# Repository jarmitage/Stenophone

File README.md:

# The Stenophone

As you can see this hasn't been worked on in a while. Nevertheless I still think about it and perhaps someone found it interesting to read so it's still here.

---

A musical instrument combining [live coding](http://toplap.org) and [stenotype](https://en.wikipedia.org/wiki/Stenotype).

Developed in the [Augmented Instruments Laboratory](http://instrumentslab.org) by [Jack Armitage](http://jackarmitage.com).

Presented at the [International Conference on Live Coding 2017](http://iclc.livecodenetwork.org/2017/), Morelia, Mexico. ([Article PDF](https://github.com/jarmitage/stenophone/raw/master/docs/stenophone_iclc2017.pdf))

## Abstract

Though laptop live coders are known to use other devices and instruments and play with other musicians, laptop live coding generally shares the common physical interface of the QWERTY keyboard. This project seeks to provide a means to explore alternatives to the QWERTY keyboard as a physical interface to laptop live coding. We present a live coding keyboard which is also a digital musical instrument, called the Stenophone. The Stenophone is an augmented stenotype or chorded keyboard, which permits continuous gestural control of keys and features an ergonomic design. These capabilities are exploited to enable the manipulation of algorithms and their parameterisation simultaneously.

## System diagram

Left: Top-down view of the Stenophone with top chassis removed, annotated with type letters and sensor/marker locations. Right: Diagram of system from mechanical input to live coding.

## Web app gif

## Citation

```bibtex
@inproceedings{armitage_stenophone:_2017,
	title = {The {Stenophone}: live coding on a chorded keyboard with continuous control},
	author = {Armitage, Jack and McPherson, Andrew},
	booktitle = {Proceedings of the {International} {Conference} on {Live} {Coding}},
	address = {Morelia, Mexico},
	url = {http://iclc.livecodenetwork.org/2017/},
	year = {2017},
	month = dec
}
```

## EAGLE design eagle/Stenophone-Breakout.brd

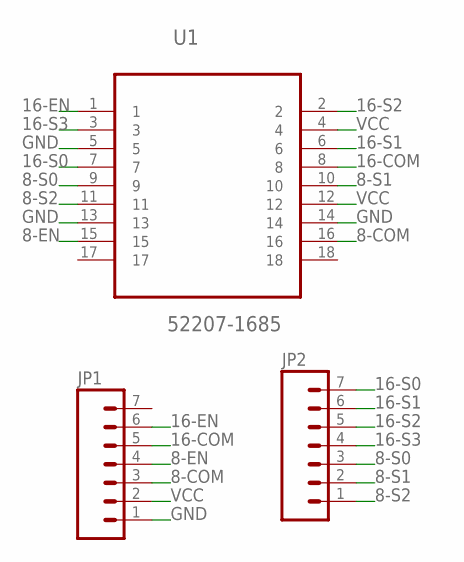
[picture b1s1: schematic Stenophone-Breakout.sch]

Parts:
JP1, JP2: M07; 1X07
U1: 52207-1685; MOLEX_52207-1685

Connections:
8-COM: JP1.3, U1.16
8-EN: JP1.4, U1.15
8-S0: JP2.3, U1.9
8-S1: JP2.2, U1.10
8-S2: JP2.1, U1.11
16-COM: JP1.5, U1.8
16-EN: JP1.6, U1.1
16-S0: JP2.7, U1.7
16-S1: JP2.6, U1.6
16-S2: JP2.5, U1.2
16-S3: JP2.4, U1.3
GND: JP1.1, U1.5, U1.13, U1.14
VCC: JP1.2, U1.4, U1.12

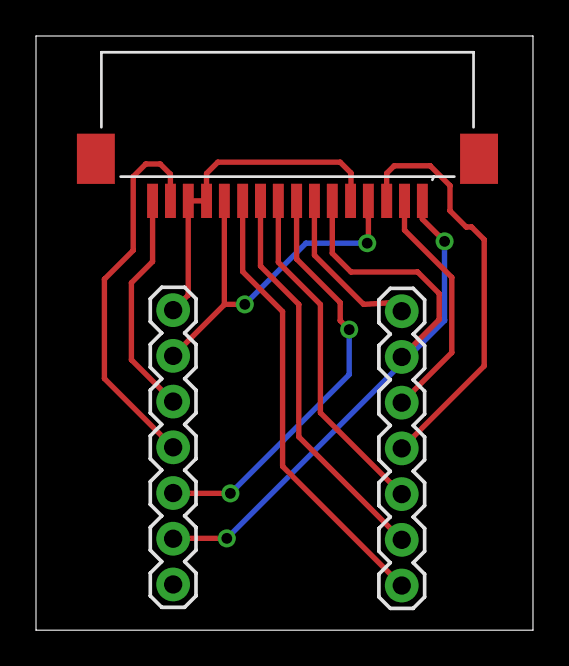
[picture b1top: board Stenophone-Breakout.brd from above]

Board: 2 copper layers, 27.6 x 33.0 mm, 3 parts (0 on the bottom side), 13 nets.

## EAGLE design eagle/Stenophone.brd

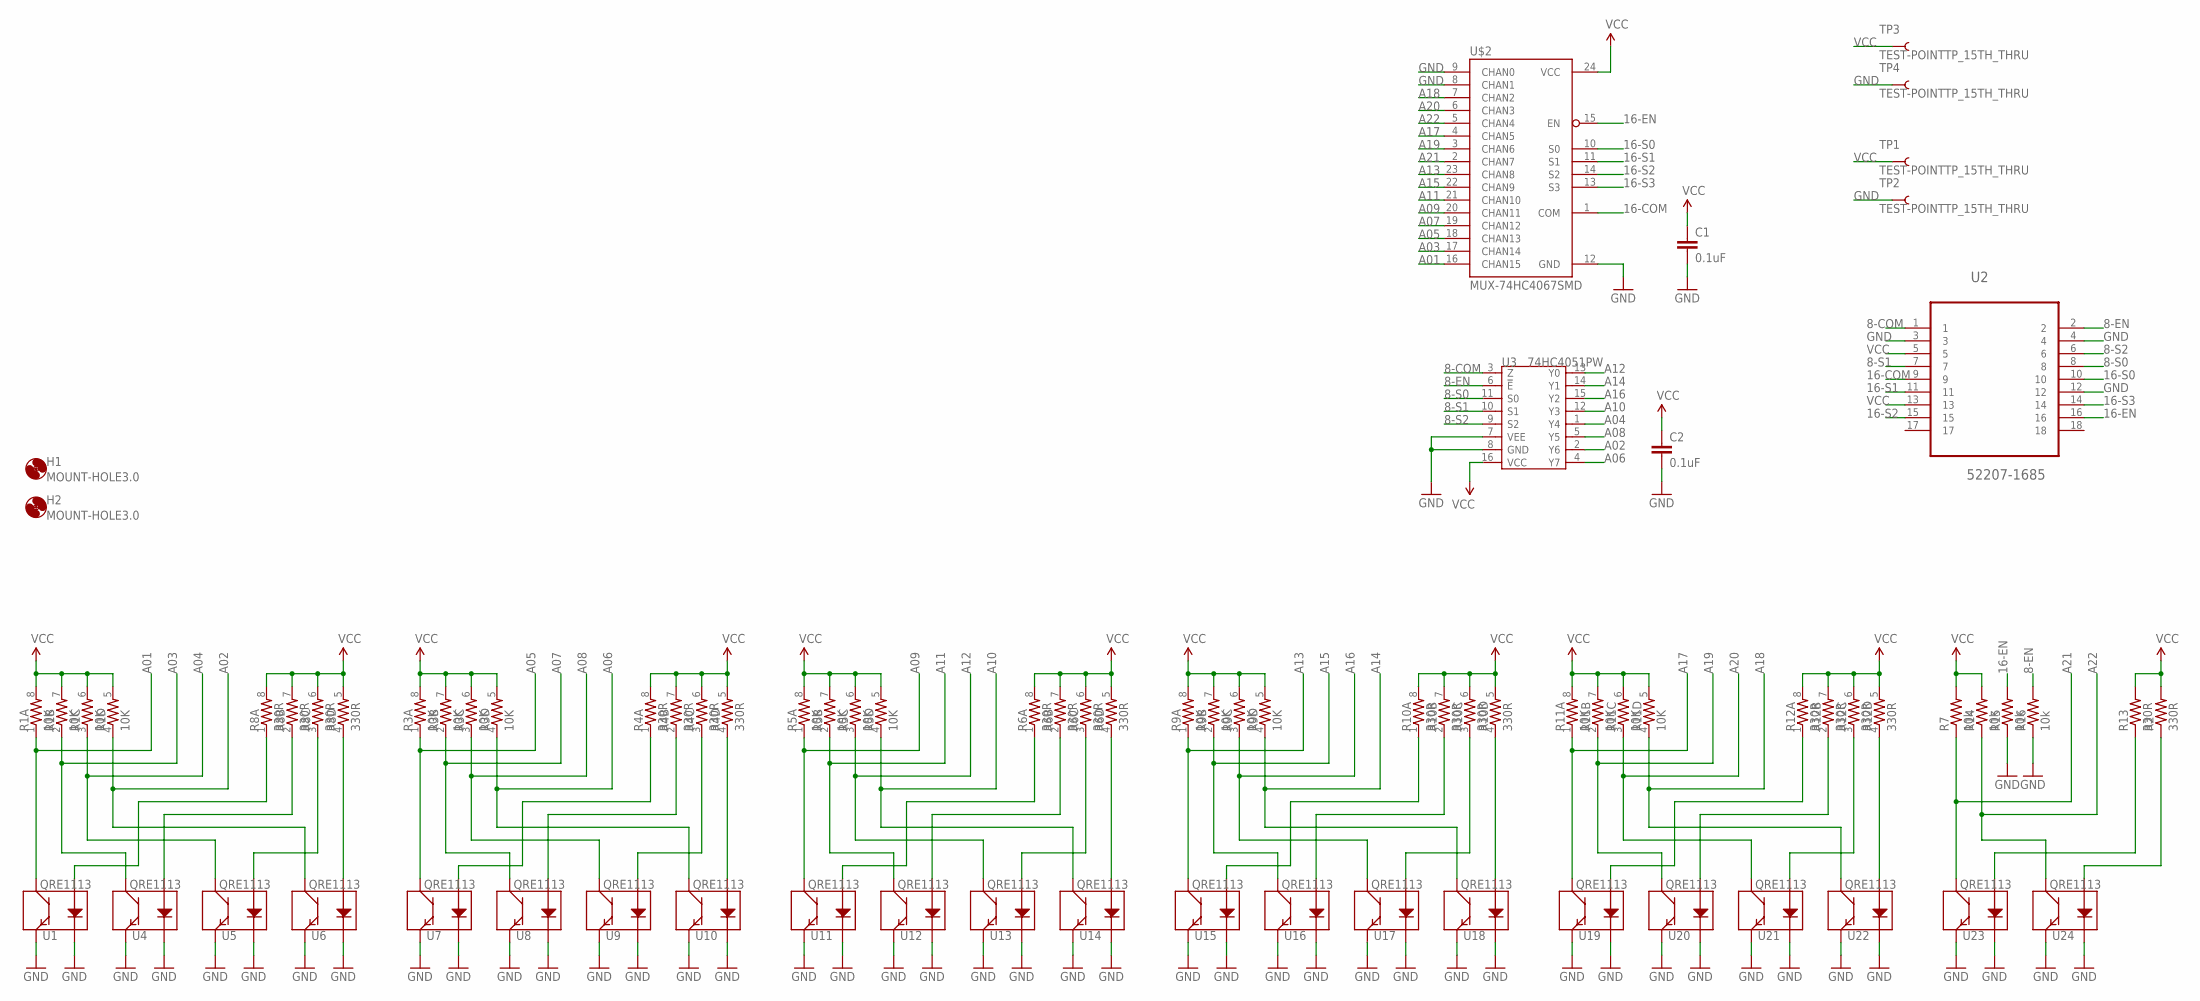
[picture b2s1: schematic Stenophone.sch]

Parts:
C1, C2: 0.1uF; 0603-CAP
H1, H2: MOUNT-HOLE3.0; 3,0
R1, R3, R5, R9, R11: 10K; 0603-ARV
R2, R13: 330R; 0603-RES
R4, R6, R8, R10, R12: 330R; 0603-ARV
R7, R14, R15, R16: 10k; 0603-RES
TP1, TP2, TP3, TP4: TEST-POINTTP_15TH_THRU; TP_15TH
U1, U4, U5, U6, U7, U8, U9, U10, U11, U12, U13, U14, U15, U16, U17, U18, U19, U20, U21, U22, U23, U24: QRE1113
U2: 52207-1685; MOLEX_52207-1685
U3: 74HC4051PW; TSSOP16-6.6
U$2: MUX-74HC4067SMD; SSOP24

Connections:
8-COM: U2.1, U3.3 (Z)
8-EN: R16.2, U2.2, U3.6 (!E)
8-S0: U2.8, U3.11 (S0)
8-S1: U2.7, U3.10 (S1)
8-S2: U2.6, U3.9 (S2)
16-COM: U2.9, U$2.1 (COM)
16-EN: R15.2, U2.16, U$2.15 (EN)
16-S0: U2.10, U$2.10 (S0)
16-S1: U2.11, U$2.11 (S1)
16-S2: U2.15, U$2.14 (S2)
16-S3: U2.14, U$2.13 (S3)
A01: R1.1, U1.3 (C), U$2.16 (CHAN15)
A02: R1.4 (1), U3.2 (Y6), U6.3 (C)
A03: R1.2 (1), U4.3 (C), U$2.17 (CHAN14)
A04: R1.3 (1), U3.1 (Y4), U5.3 (C)
A05: R3.1, U7.3 (C), U$2.18 (CHAN13)
A06: R3.4 (1), U3.4 (Y7), U10.3 (C)
A07: R3.2 (1), U8.3 (C), U$2.19 (CHAN12)
A08: R3.3 (1), U3.5 (Y5), U9.3 (C)
A09: R5.1, U11.3 (C), U$2.20 (CHAN11)
A10: R5.4 (1), U3.12 (Y3), U14.3 (C)
A11: R5.2 (1), U12.3 (C), U$2.21 (CHAN10)
A12: R5.3 (1), U3.13 (Y0), U13.3 (C)
A13: R9.1, U15.3 (C), U$2.23 (CHAN8)
A14: R9.4 (1), U3.14 (Y1), U18.3 (C)
A15: R9.2 (1), U16.3 (C), U$2.22 (CHAN9)
A16: R9.3 (1), U3.15 (Y2), U17.3 (C)
A17: R11.1, U19.3 (C), U$2.4 (CHAN5)
A18: R11.4 (1), U22.3 (C), U$2.7 (CHAN2)
A19: R11.2 (1), U20.3 (C), U$2.3 (CHAN6)
A20: R11.3 (1), U21.3 (C), U$2.6 (CHAN3)
A21: R7.1, U23.3 (C), U$2.2 (CHAN7)
A22: R14.1, U24.3 (C), U$2.5 (CHAN4)
GND: C1.2, C2.2, R15.1, R16.1, TP2.P$1, TP4.P$1, U1.2 (K), U1.4 (E), U2.3, U2.4, U2.12, U3.7 (VEE), U3.8 (GND), U4.2 (K), U4.4 (E), U5.2 (K), U5.4 (E), U6.2 (K), U6.4 (E), U7.2 (K), U7.4 (E), U8.2 (K), U8.4 (E), U9.2 (K), U9.4 (E), U10.2 (K), U10.4 (E), U11.2 (K), U11.4 (E), U12.2 (K), U12.4 (E), U13.2 (K), U13.4 (E), U14.2 (K), U14.4 (E), U15.2 (K), U15.4 (E), U16.2 (K), U16.4 (E), U17.2 (K), U17.4 (E), U18.2 (K), U18.4 (E), U19.2 (K), U19.4 (E), U20.2 (K), U20.4 (E), U21.2 (K), U21.4 (E), U22.2 (K), U22.4 (E), U23.2 (K), U23.4 (E), U24.2 (K), U24.4 (E), U$2.8 (CHAN1), U$2.9 (CHAN0), U$2.12 (GND)
unnamed: R8.4 (1), U6.1 (A)
unnamed: R8.3 (1), U5.1 (A)
unnamed: R8.1, U1.1 (A)
unnamed: R8.2 (1), U4.1 (A)
unnamed: R4.4 (1), U10.1 (A)
unnamed: R4.3 (1), U9.1 (A)
unnamed: R4.1, U7.1 (A)
unnamed: R4.2 (1), U8.1 (A)
unnamed: R6.4 (1), U14.1 (A)
unnamed: R6.3 (1), U13.1 (A)
unnamed: R6.1, U11.1 (A)
unnamed: R6.2 (1), U12.1 (A)
unnamed: R10.4 (1), U18.1 (A)
unnamed: R10.3 (1), U17.1 (A)
unnamed: R10.1, U15.1 (A)
unnamed: R10.2 (1), U16.1 (A)
unnamed: R12.4 (1), U22.1 (A)
unnamed: R12.3 (1), U21.1 (A)
unnamed: R12.1, U19.1 (A)
unnamed: R12.2 (1), U20.1 (A)
unnamed: R2.1, U24.1 (A)
unnamed: R13.1, U23.1 (A)
VCC: C1.1, C2.1, R1.5 (2), R1.6 (2), R1.7 (2), R1.8 (2), R2.2, R3.5 (2), R3.6 (2), R3.7 (2), R3.8 (2), R4.5 (2), R4.6 (2), R4.7 (2), R4.8 (2), R5.5 (2), R5.6 (2), R5.7 (2), R5.8 (2), R6.5 (2), R6.6 (2), R6.7 (2), R6.8 (2), R7.2, R8.5 (2), R8.6 (2), R8.7 (2), R8.8 (2), R9.5 (2), R9.6 (2), R9.7 (2), R9.8 (2), R10.5 (2), R10.6 (2), R10.7 (2), R10.8 (2), R11.5 (2), R11.6 (2), R11.7 (2), R11.8 (2), R12.5 (2), R12.6 (2), R12.7 (2), R12.8 (2), R13.2, R14.2, TP1.P$1, TP3.P$1, U2.5, U2.13, U3.16 (VCC), U$2.24 (VCC)

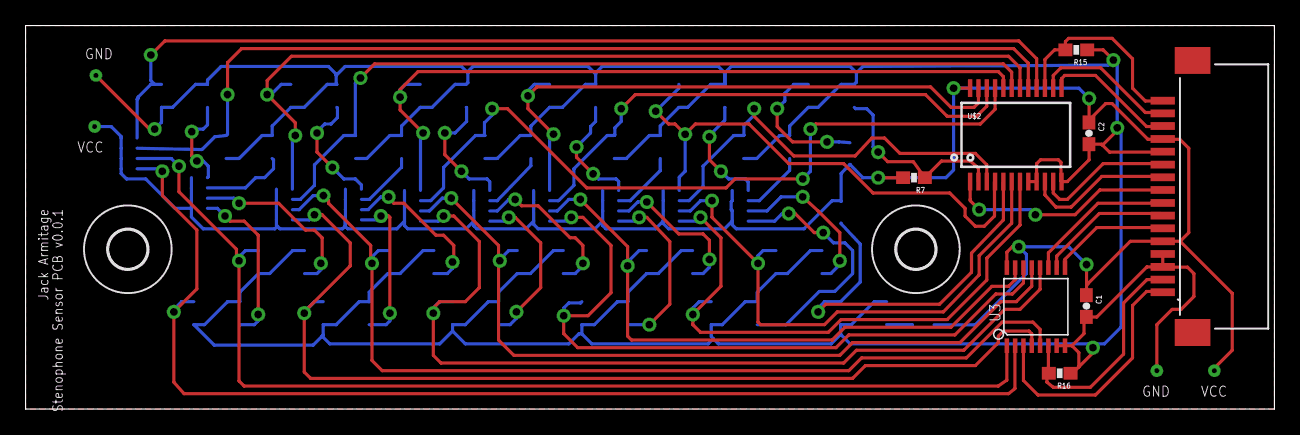
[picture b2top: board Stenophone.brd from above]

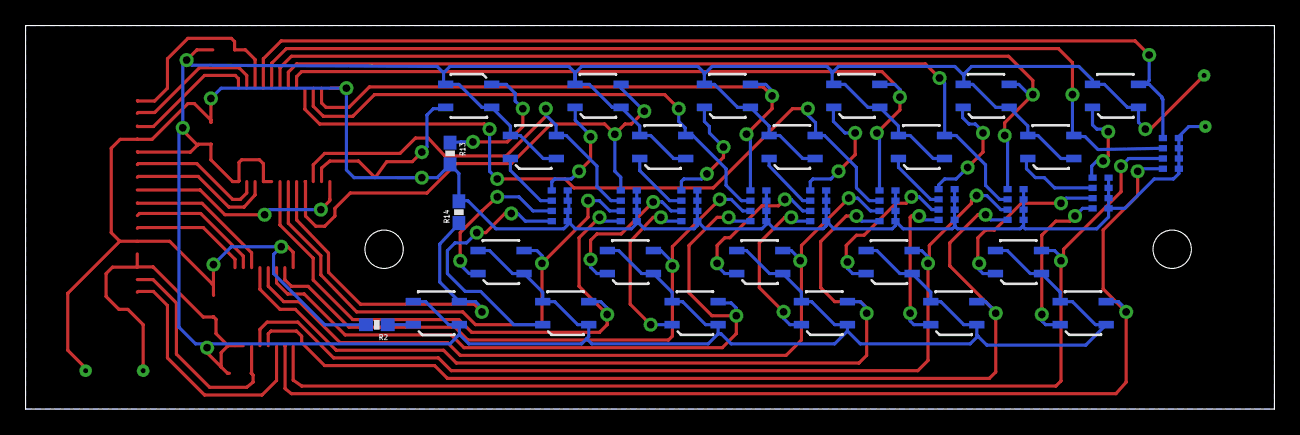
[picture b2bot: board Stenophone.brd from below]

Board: 2 copper layers, 97.7 x 30.0 mm, 49 parts (35 on the bottom side), 57 nets.

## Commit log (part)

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2017-12-02 server in progress
2017-12-02 socket working
2017-12-02 basic vis
2017-12-02 v1 web interface
2017-12-02 sensor smoothing and chord holding
2017-12-02 added textbox to page;
2017-12-02 added code and design documentation
2017-12-02 added web readme
2017-12-02 added diagram jpg
2018-11-15 who knows
2020-02-01 Bump extend from 3.0.1 to 3.0.2 in /web
    Bumps [extend](https://github.com/justmoon/node-extend) from 3.0.1 to 3.0.2.
    - [Release notes](https://github.com/justmoon/node-extend/releases)
    - [Changelog](https://github.com/justmoon/node-extend/blob/master/CHANGELOG.md)
    - [Commits](https://github.com/justmoon/node-extend/compare/v3.0.1...v3.0.2)
2020-02-01 Bump stringstream from 0.0.5 to 0.0.6 in /web
    Bumps [stringstream](https://github.com/mhart/StringStream) from 0.0.5 to 0.0.6.
    - [Release notes](https://github.com/mhart/StringStream/releases)
    - [Commits](https://github.com/mhart/StringStream/compare/v0.0.5...v0.0.6)
2020-02-01 Bump sshpk from 1.13.1 to 1.16.1 in /web
    Bumps [sshpk](https://github.com/joyent/node-sshpk) from 1.13.1 to 1.16.1.
    - [Release notes](https://github.com/joyent/node-sshpk/releases)
    - [Commits](https://github.com/joyent/node-sshpk/compare/v1.13.1...v1.16.1)
2020-02-01 Bump fstream from 1.0.11 to 1.0.12 in /web
    Bumps [fstream](https://github.com/npm/fstream) from 1.0.11 to 1.0.12.
    - [Release notes](https://github.com/npm/fstream/releases)
    - [Commits](https://github.com/npm/fstream/compare/v1.0.11...v1.0.12)
2020-02-01 Bump tar-fs from 1.16.0 to 1.16.3 in /web
    Bumps [tar-fs](https://github.com/mafintosh/tar-fs) from 1.16.0 to 1.16.3.
    - [Release notes](https://github.com/mafintosh/tar-fs/releases)
    - [Commits](https://github.com/mafintosh/tar-fs/compare/v1.16.0...v1.16.3)
2020-02-01 Bump tar from 2.2.1 to 2.2.2 in /web
    Bumps [tar](https://github.com/npm/node-tar) from 2.2.1 to 2.2.2.
    - [Release notes](https://github.com/npm/node-tar/releases)
    - [Changelog](https://github.com/npm/node-tar/blob/master/CHANGELOG.md)
    - [Commits](https://github.com/npm/node-tar/compare/v2.2.1...v2.2.2)
2020-04-05 Bump acorn from 5.2.1 to 5.7.4 in /web
    Bumps [acorn](https://github.com/acornjs/acorn) from 5.2.1 to 5.7.4.
    - [Release notes](https://github.com/acornjs/acorn/releases)
    - [Commits](https://github.com/acornjs/acorn/compare/5.2.1...5.7.4)
2020-12-11 Bump ini from 1.3.5 to 1.3.7 in /web
    Bumps [ini](https://github.com/isaacs/ini) from 1.3.5 to 1.3.7.
    - [Release notes](https://github.com/isaacs/ini/releases)
    - [Commits](https://github.com/isaacs/ini/compare/v1.3.5...v1.3.7)
2021-01-21 Bump socket.io from 2.0.4 to 2.4.0 in /web
    Bumps [socket.io](https://github.com/socketio/socket.io) from 2.0.4 to 2.4.0.
    - [Release notes](https://github.com/socketio/socket.io/releases)
    - [Changelog](https://github.com/socketio/socket.io/blob/2.4.0/CHANGELOG.md)
    - [Commits](https://github.com/socketio/socket.io/compare/2.0.4...2.4.0)
2021-08-11 Bump path-parse from 1.0.5 to 1.0.7 in /web
    Bumps [path-parse](https://github.com/jbgutierrez/path-parse) from 1.0.5 to 1.0.7.
    - [Release notes](https://github.com/jbgutierrez/path-parse/releases)
    - [Commits](https://github.com/jbgutierrez/path-parse/commits/v1.0.7)
    ---
    updated-dependencies:
    - dependency-name: path-parse
2022-12-06 Bump qs from 6.4.0 to 6.4.1 in /web
    Bumps [qs](https://github.com/ljharb/qs) from 6.4.0 to 6.4.1.
    - [Release notes](https://github.com/ljharb/qs/releases)
    - [Changelog](https://github.com/ljharb/qs/blob/main/CHANGELOG.md)
    - [Commits](https://github.com/ljharb/qs/compare/v6.4.0...v6.4.1)
    ---
    updated-dependencies:
2026-03-29 Bump brace-expansion from 1.1.11 to 1.1.13 in /web
    Bumps [brace-expansion](https://github.com/juliangruber/brace-expansion) from 1.1.11 to 1.1.13.
    - [Release notes](https://github.com/juliangruber/brace-expansion/releases)
    - [Commits](https://github.com/juliangruber/brace-expansion/compare/1.1.11...v1.1.13)
    ---
    updated-dependencies:
    - dependency-name: brace-expansion

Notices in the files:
parts and their libraries:
SparkFun-Connectors: Licensing: Creative Commons ShareAlike 4.0 International - https://creativecommons.org/licenses/by-sa/4.0
